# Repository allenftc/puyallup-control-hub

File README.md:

# Puyallup to Earth, Puyallup to Earth, can anyone hear me?
## No, because the loop times on REV control hubs are cooked. 30Hz should not be the standard for a control system. Even the EV3 is faster 💀💀💀
I am making the Puyallup Control Hub for fun just to see how overkill I can make a similar type of thing but for cheaper and more powerful, as well as smaller.

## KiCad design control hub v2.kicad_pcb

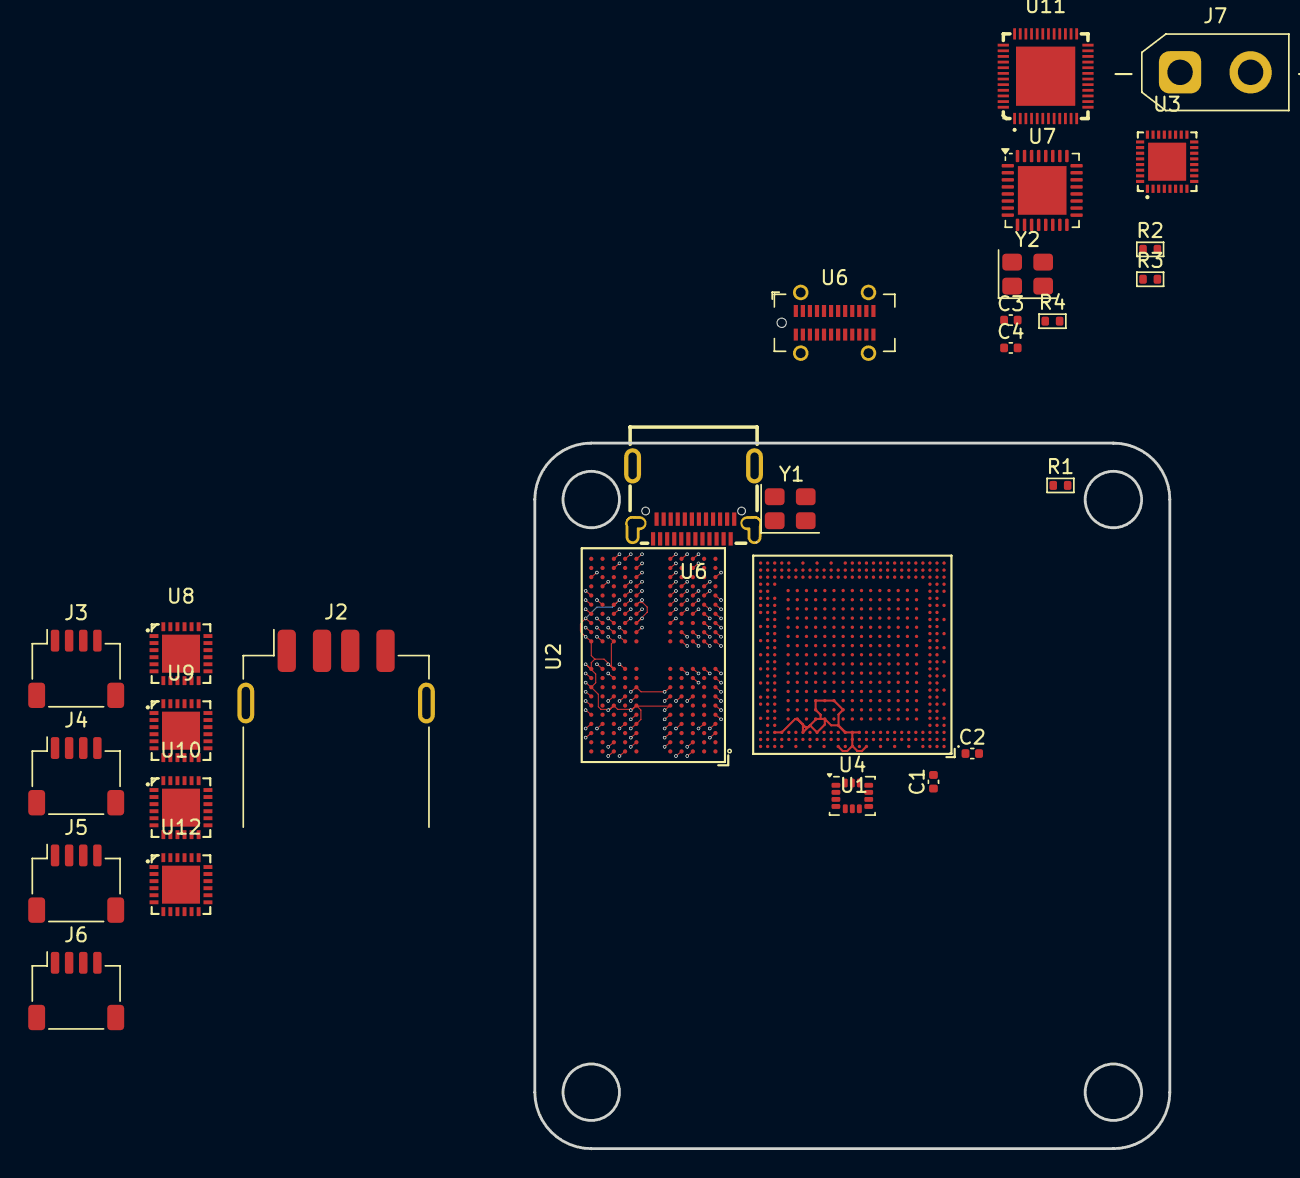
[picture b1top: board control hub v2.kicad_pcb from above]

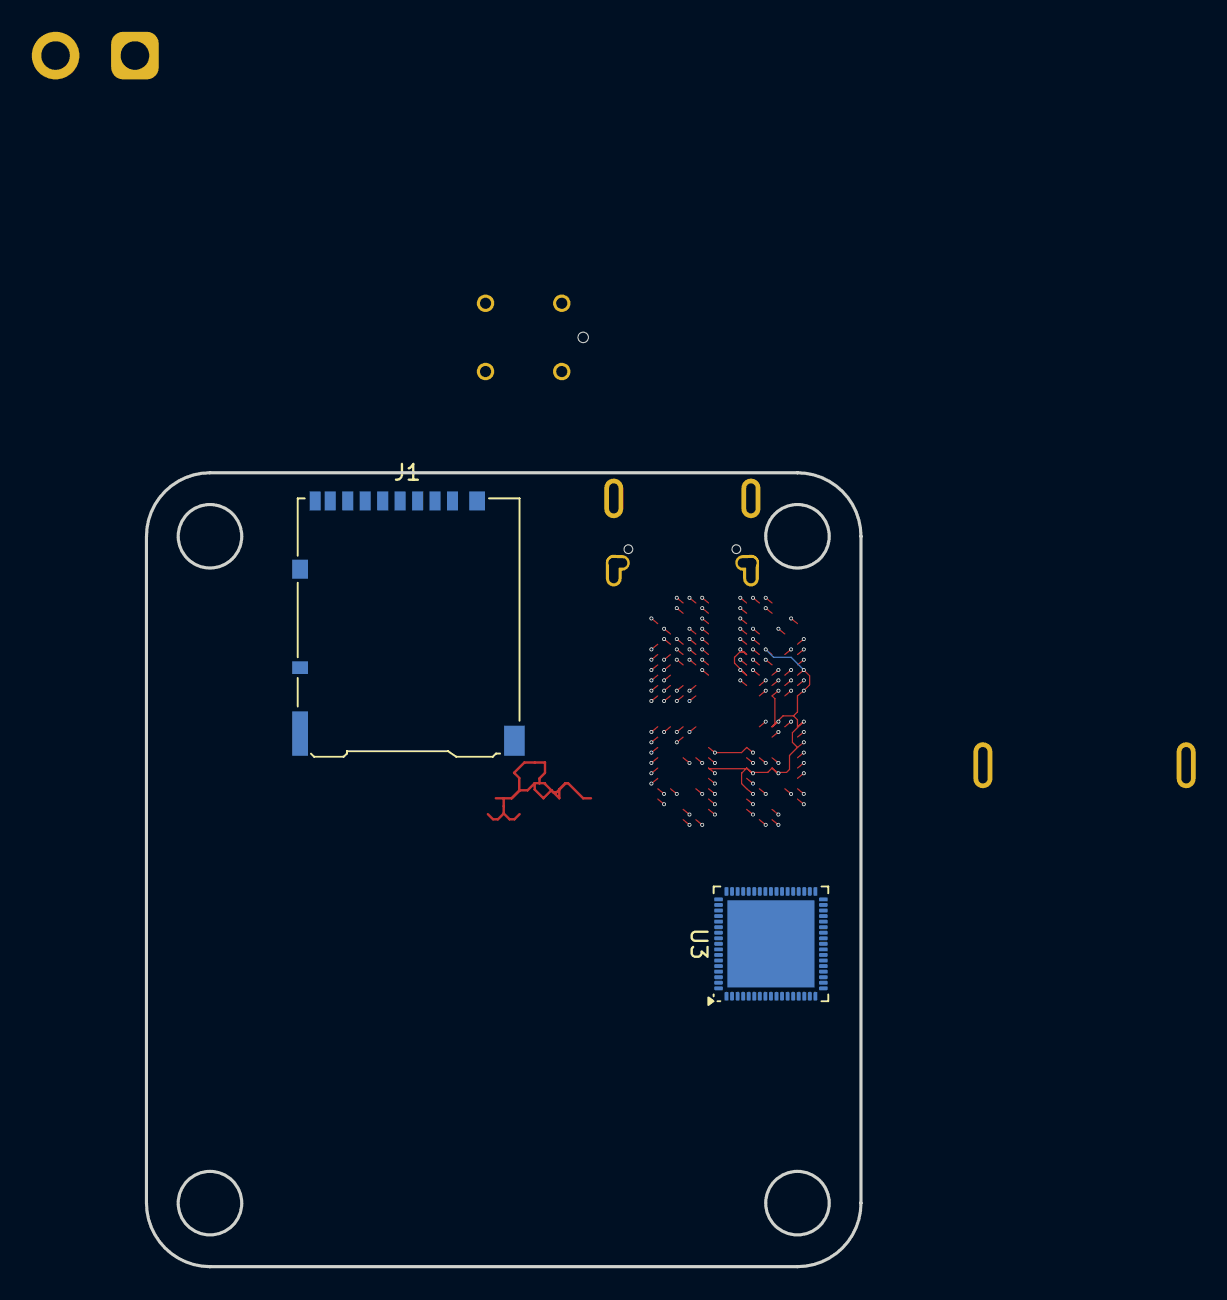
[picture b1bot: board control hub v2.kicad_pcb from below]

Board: 4 copper layers, 45.0 x 50.0 mm, 30 parts (2 on the bottom side), 98 nets.

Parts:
C1, C2, C3, C4: 18pF; C_0402_1005Metric
J1: Micro_SD_Card_Det2; microSD_HC_Hirose_DM3AT-SF-PEJM5
J2: USB_A; USB_A_Receptacle_GCT_USB1046
J3, J4, J5, J6: Conn_01x04_Socket; JST_SH_SM04B-SRSS-TB_1x04-1MP_P1.00mm_Horizontal
J7: Conn_01x02; AMASS_XT30UPB-M_1x02_P5.0mm_Vertical
R1, R4: 1M; R_0402_1005Metric
R2, R3: 240R; R_0402_1005Metric
U1: RK3562; BGA-478_L13.9-W13.9_RK3562
U2: H9HCNNNBKUMLXR-NEE; FBGA-200_L15.0-W10.0-BL_H9HCNNNBKUMLXR
U3: RT9992ZQW; WQFN-32_L4.0-W4.0-P0.40-BL-EP
U3#2: RK808-B; ArtInChip_QFN-68-1EP_7x7mm_P0.35mm_EP5.49x5.49mm
U4: LSM6DS3; LGA-14_3x2.5mm_P0.5mm_LayoutBorder3x4y
U6: GT-USB-7013A03; USB-C-SMD_GT-USB-7013A03
U6#2: GT-USB-7013A03; USB_C_Receptacle_GCT_USB4115-03-C
U7: STM32G431KBUx; QFN-32-1EP_5x5mm_P0.5mm_EP3.45x3.45mm
U8, U9, U10, U12: G2061Q; QFN-24_L4.0-W4.0-P0.50-TL-EP2.7
U11: RTL8723DS-CG; WQFN-48_L6.0-W6.0-P0.40-BL-EP4.2
Y1, Y2: 24; Crystal_SMD_3225-4Pin_3.2x2.5mm

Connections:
0V9: U1.1E12 (VDD_GPU_1), U1.1F11 (VDD_GPU_2), U1.1F12 (VDD_GPU_3), U1.1F13 (VDD_GPU_4), U1.1G3 (VDD_NPU_1), U1.1G4 (VDD_NPU_2), U1.1G5 (VDD_NPU_3), U1.1G8 (VDD_CPU_1), U1.1G10 (VDD_LOGIC_1), U1.1G11 (VDD_GPU_5), U1.1G12 (VDD_GPU_6), U1.1H3 (VDD_NPU_4), U1.1H4 (VDD_NPU_5), U1.1H6 (VDD_CPU_2), U1.1H7 (VDD_CPU_3), U1.1H8 (VDD_CPU_4), U1.1H10 (VDD_LOGIC_2), U1.1H11 (VDD_LOGIC_MEM), U1.1J6 (VDD_CPU_5), U1.1J7 (VDD_CPU_6), U1.1J10 (VDD_LOGIC_3), U1.1J11 (VDD_LOGIC_4), U1.1J12 (VDD_LOGIC_5), U1.1K10 (VDD_LOGIC_6), U1.1K14 (MULTI_PHY_AVDD_0V9), U1.1L6 (MIPI_CSI_RX1_AVDD_0V9), U1.1L8 (MIPI_CSI_RX0_AVDD_0V9), U1.1L14 (USB_AVDD_0V9), U1.1M9 (MIPI_DSI_TX/LVDS_TX_AVDD_0V9), U1.1M10 (SYSPLL_AVDD_0V9), U1.1M11 (PMU_VDD_LOGIC_0V9), U1.1M13 (PMUPLL_AVDD_0V9)
+1V1: U1.1D6 (DDRPHY_VDDQ_3), U1.1D11 (DDRPHY_VDDQ_6), U1.1E3 (DDRPHY_VDDQ_1), U1.1E4 (DDRPHY_VDDQL_1), U1.1E5 (DDRPHY_VDDQ_2), U1.1E6 (DDRPHY_VDDQL_2), U1.1E7 (DDRPHY_VDDQ_4), U1.1E8 (DDRPHY_VDDQL_3), U1.1E9 (DDRPHY_VDDQ_5)
+1V1_DDR: R2.1, R3.1, U2.A4 (VDD2), U2.A9 (VDD2), U2.AA3 (VDDQ), U2.AA5 (VDDQ), U2.AA8 (VDDQ), U2.AA10 (VDDQ), U2.AB4 (VDD2), U2.AB9 (VDD2), U2.B3 (VDDQ), U2.B5 (VDDQ), U2.B8 (VDDQ), U2.B10 (VDDQ), U2.D1 (VDDQ), U2.D5 (VDDQ), U2.D8 (VDDQ), U2.D12 (VDDQ), U2.F3 (VDDQ), U2.F5 (VDD2), U2.F8 (VDD2), U2.F10 (VDDQ), U2.H1 (VDD2), U2.H5 (VDD2), U2.H8 (VDD2), U2.H12 (VDD2), U2.K1 (VDD2), U2.K3 (VDD2), U2.K10 (VDD2), U2.K12 (VDD2), U2.N1 (VDD2), U2.N3 (VDD2), U2.N10 (VDD2), U2.N12 (VDD2), U2.R1 (VDD2), U2.R5 (VDD2), U2.R8 (VDD2), U2.R12 (VDD2), U2.U3 (VDDQ), U2.U5 (VDD2), U2.U8 (VDD2), U2.U10 (VDDQ), U2.W1 (VDDQ), U2.W5 (VDDQ), U2.W8 (VDDQ), U2.W12 (VDDQ)
+1V8: U1.1E14 (SARADC0_AVDD_1V8), U1.1E15 (OTP_VCC_1V8), U1.1G1 (SYSPLL_AVDD_1V8), U1.1H14 (VCCIO4), U1.1K2 (SARADC1_AVDD_1V8), U1.1K3 (VCCIO5), U1.1K15 (MULTI_PHY_AVDD_1V8), U1.1L5 (VCCIO6_2), U1.1L11 (PMUIO1), U1.1L13 (PMUPLL_AVDD_1V8), U1.1M4 (VCCIO6_1), U1.1M7 (MIPI_CSI_RX1_AVDD_1V8), U1.1M8 (MIPI_CSI_RX0_AVDD_1V8), U1.1M15 (USB_AVDD_1V8), U1.1N9 (MIPI_DSI_TX/LVDS_TX_AVDD_1V8)
+1V8_DDR: U2.F1 (VDD1), U2.F12 (VDD1), U2.G4 (VDD1), U2.G9 (VDD1), U2.T4 (VDD1), U2.T9 (VDD1), U2.U1 (VDD1), U2.U12 (VDD1)
+3.3V: J3.3, J4.3, J5.3, J6.3, U4.5 (VDDIO), U4.8 (VDD)
+3V3: J1.4 (VDD), U1.1F14 (VCCIO2), U1.1G15 (VCCIO3), U1.1L3 (VCCIO1), U1.1L12 (PMUIO0), U1.1M14 (USB_AVDD_3V3), U7.1 (VDD), U7.15 (VDDA), U7.17 (VDD)
+BATT: J7.1, U3.29 (BAT)
/Memory/DDR.A.a0: U1.B10 (AC11/DDR4_A11/LPDDR4_A0_A/DDR3_A6/LPDDR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), U2.H2 (CA0a)
/Memory/DDR.A.a1: U1.A10 (AC2/DDR4_A2/LPDDR4_A1_A/DDR3_A4/LPDDR3_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), U2.J2 (CA1a)
/Memory/DDR.A.a2: U1.C10 (AC15/DDR4_A15_CASN/LPDDR4_A2_A/DDR3_A0/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), U2.H9 (CA2a)
/Memory/DDR.A.a3: U1.1A6 (AC12/DDR4_A12/LPDDR4_A3_A/DDR3_BA0), U2.H10 (CA3a)
/Memory/DDR.A.a4: U1.1B8 (AC14/DDR4_A14_WEN/LPDDR4_A4_A/DDR3_A15), U2.H11 (CA4a)
/Memory/DDR.A.a5: U1.1A7 (AC16/DDR4_A16_RASN/LPDDR4_A5_A/DDR3_RASN), U2.J11 (CA5a)
/Memory/DDR.A.b0: U1.B18 (AC7/DDR4_A7/LPDDR4_A0_B/DDR3_A5/LPDDR3_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), U2.R2 (CA0b)
/Memory/DDR.A.b1: U1.A18 (AC6/DDR4_A6/LPDDR4_A1_B/DDR3_A14/LPDDR3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), U2.P2 (CA1b)
/Memory/DDR.A.b2: U1.C18 (AC18/DDR4_BA0/LPDDR4_A2_B/DDR3_A1/LPDDR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), U2.R9 (CA2b)
/Memory/DDR.A.b3: U1.1A10 (AC4/DDR4_A4/LPDDR4_A3_B/DDR3_BA1), U2.R10 (CA3b)
/Memory/DDR.A.b4: U1.1A9 (AC19/DDR4_BA1/LPDDR4_A4_B/DDR3_A12), U2.R11 (CA4b)
/Memory/DDR.A.b5: U1.1A8 (AC5/DDR4_A5/LPDDR4_A5_B/DDR3_A11), U2.P11 (CA5b)
/Memory/DDR.CKEa0: U1.C12 (AC22/DDR4_CKE0/LPDDR4_CKE0_A/DDR3_CKE/L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), U2.J4 (CKE0a)
/Memory/DDR.CKEb0: U1.C16 (AC10/DDR4_A10/LPDDR4_CKE0_B/DDR3_A10/LP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), U2.P4 (CKE0b)
/Memory/DDR.CLKa+: U1.B13 (AC24/DDR4_CLK0N/LPDDR4_CLKP_A/DDR3_CLKN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), U2.J8 (CK_ta)
/Memory/DDR.CLKa-: U1.A13 (AC23/DDR4_CLK0P/LPDDR4_CLKN_A/DDR3_CLKP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), U2.J9 (CK_ca)
/Memory/DDR.CLKb+: U1.B15 (AC9/DDR4_A9/LPDDR4_CLKP_B/DDR3_A13), U2.P8 (CK_tb)
/Memory/DDR.CLKb-: U1.A15 (AC0/DDR4_A0/LPDDR4_CLKN_B/DDR3_A9), U2.P9 (CK_cb)
/Memory/DDR.CS0A: U1.B11 (AC3/DDR4_A3/LPDDR4_CS0N_A/DDR3_ODT1/LPD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), U2.H4 (CS0a)
/Memory/DDR.CS0B: U1.B17 (AC28/DDR4_ODT1/LPDDR4_CS0N_B/DDR3_CS0N/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), U2.R4 (CS0b)
/Memory/DDR.DMA0: U1.B7 (DDR_DM0_A/DDR4_DML_A/LPDDR4_DM0_A/DDR3_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), U2.C3 (DMI0a)
/Memory/DDR.DMA1: U1.A2 (DDR_DM1_A/DDR4_DMU_A/LPDDR4_DM1_A/DDR3_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), U2.C10 (DMI1a)
/Memory/DDR.DMB1: U1.A26 (DDR_DM1_B/DDR4_DML_B/LPDDR4_DM1_B/DDR3_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), U2.Y10 (DMI1b)
/Memory/DDR.DQSa+0: U1.1A3 (DDR_DQS0P_A/DDR4_DQSL_P_A/LPDDR4_DQS0P_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), U2.D3 (DQS0_ta)
/Memory/DDR.DQSa+1: U1.1A1 (DDR_DQS1P_A/DDR4_DQSU_P_A/LPDDR4_DQS1P_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), U2.D10 (DQS1_ta)
/Memory/DDR.DQSa-0: U1.1B3 (DDR_DQS0N_A/DDR4_DQSL_N_A/LPDDR4_DQS0N_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), U2.E3 (DQS0_ca), U2.V3 (DQS0_cb)
/Memory/DDR.DQSa-1: U1.1B1 (DDR_DQS1N_A/DDR4_DQSU_N_A/LPDDR4_DQS1N_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), U2.E10 (DQS1_ca)
/Memory/DDR.DQSb+0: U1.1A13 (DDR_DQS0P_B/DDR4_DQSU_P_B/LPDDR4_DQS0P_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), U2.W3 (DQS0_tb)
/Memory/DDR.DQSb+1: U1.1A15 (DDR_DQS1P_B/DDR4_DQSL_P_B/LPDDR4_DQS1P_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), U2.W10 (DQS1_tb)
/Memory/DDR.DQSb-1: U1.1B15 (DDR_DQS1N_B/DDR4_DQSL_N_B/LPDDR4_DQS1N_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), U2.V10 (DQS1_cb)
/Memory/DDR.DQa0: U1.B6 (DDR_DQ0_A/DDR4_DQL6_A/LPDDR4_DQ0_A/DDR3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), U2.B2 (DQ0a)
/Memory/DDR.DQa1: U1.B8 (DDR_DQ1_A/DDR4_DQL2_A/LPDDR4_DQ1_A/DDR3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), U2.C2 (DQ1a)
/Memory/DDR.DQa2: U1.A8 (DDR_DQ2_A/DDR4_DQL0_A/LPDDR4_DQ2_A/DDR3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), U2.E2 (DQ2a)
/Memory/DDR.DQa3: U1.C8 (DDR_DQ3_A/DDR4_DQL4_A/LPDDR4_DQ3_A/DDR3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), U2.F2 (DQ3a)
/Memory/DDR.DQa4: U1.C5 (DDR_DQ4_A/DDR4_DQL5_A/LPDDR4_DQ4_A/DDR3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), U2.F4 (DQ4a)
/Memory/DDR.DQa5: U1.B5 (DDR_DQ5_A/DDR4_DQL1_A/LPDDR4_DQ5_A/DDR3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), U2.E4 (DQ5a)
/Memory/DDR.DQa6: U1.A6 (DDR_DQ6_A/DDR4_DQL7_A/LPDDR4_DQ6_A/DDR3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), U2.C4 (DQ6a)
/Memory/DDR.DQa7: U1.C6 (DDR_DQ7_A/DDR4_DQL3_A/LPDDR4_DQ7_A/DDR3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), U2.B4 (DQ7a)
/Memory/DDR.DQa8: U1.C2 (DDR_DQ8_A/DDR4_DQU1_A/LPDDR4_DQ8_A/DDR3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), U2.B11 (DQ8a)
/Memory/DDR.DQa9: U1.C1 (DDR_DQ9_A/DDR4_DQU5_A/LPDDR4_DQ9_A/DDR3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), U2.C11 (DQ9a)
/Memory/DDR.DQa10: U1.B1 (DDR_DQ10_A/DDR4_DQU3_A/LPDDR4_DQ10_A/DD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), U2.E11 (DQ10a)
/Memory/DDR.DQa11: U1.B2 (DDR_DQ11_A/DDR4_DQU7_A/LPDDR4_DQ11_A/DD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), U2.F11 (DQ11a)
/Memory/DDR.DQa12: U1.A4 (DDR_DQ12_A/DDR4_DQU0_A/LPDDR4_DQ12_A/DD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), U2.F9 (DQ12a)
/Memory/DDR.DQa13: U1.B4 (DDR_DQ13_A/DDR4_DQU4_A/LPDDR4_DQ13_A/DD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), U2.E9 (DQ13a)
/Memory/DDR.DQa14: U1.A3 (DDR_DQ14_A/DDR4_DQU2_A/LPDDR4_DQ14_A/DD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), U2.C9 (DQ14a)
/Memory/DDR.DQa15: U1.B3 (DDR_DQ15_A/DDR4_DQU6_A/LPDDR4_DQ15_A/DD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), U2.B9 (DQ15a)
/Memory/DDR.DQb0: U1.B22 (DDR_DQ0_B/DDR4_DQU7_B/LPDDR4_DQ0_B/DDR3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), U2.AA2 (DQ0b)
/Memory/DDR.DQb1: U1.B20 (DDR_DQ1_B/DDR4_DQU3_B/LPDDR4_DQ1_B/DDR3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), U2.Y2 (DQ1b)
/Memory/DDR.DQb2: U1.A20 (DDR_DQ2_B/DDR4_DQU1_B/LPDDR4_DQ2_B/DDR3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), U2.V2 (DQ2b)
/Memory/DDR.DQb3: U1.C20 (DDR_DQ3_B/DDR4_DQU5_B/LPDDR4_DQ3_B/DDR3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), U2.U2 (DQ3b)
/Memory/DDR.DQb4: U1.C23 (DDR_DQ4_B/DDR4_DQU0_B/LPDDR4_DQ4_B/DDR3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), U2.U4 (DQ4b)
/Memory/DDR.DQb5: U1.B23 (DDR_DQ5_B/DDR4_DQU4_B/LPDDR4_DQ5_B/DDR3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), U2.V4 (DQ5b)
/Memory/DDR.DQb6: U1.C22 (DDR_DQ6_B/DDR4_DQU2_B/LPDDR4_DQ6_B/DDR3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), U2.Y4 (DQ6b)
/Memory/DDR.DQb7: U1.A22 (DDR_DQ7_B/DDR4_DQU6_B/LPDDR4_DQ7_B/DDR3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), U2.AA4 (DQ7b)
/Memory/DDR.DQb8: U1.C26 (DDR_DQ8_B/DDR4_DQL0_B/LPDDR4_DQ8_B/DDR3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), U2.AA11 (DQ8b)
/Memory/DDR.DQb9: U1.C27 (DDR_DQ9_B/DDR4_DQL4_B/LPDDR4_DQ9_B/DDR3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), U2.Y11 (DQ9b)
/Memory/DDR.DQb10: U1.B27 (DDR_DQ10_B/DDR4_DQL2_B/LPDDR4_DQ10_B/DD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), U2.V11 (DQ10b)
/Memory/DDR.DQb11: U1.B26 (DDR_DQ11_B/DDR4_DQL6_B/LPDDR4_DQ11_B/DD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), U2.U11 (DQ11b)
/Memory/DDR.DQb12: U1.A24 (DDR_DQ12_B/DDR4_DQL5_B/LPDDR4_DQ12_B/DD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), U2.U9 (DQ12b)
/Memory/DDR.DQb13: U1.B24 (DDR_DQ13_B/DDR4_DQL7_B/LPDDR4_DQ13_B/DD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), U2.V9 (DQ13b)
/Memory/DDR.DQb14: U1.A25 (DDR_DQ14_B/DDR4_DQL1_B/LPDDR4_DQ14_B/DD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), U2.Y9 (DQ14b)
/Memory/DDR.DQb15: U1.B25 (DDR_DQ15_B/DDR4_DQL3_B/LPDDR4_DQ15_B/DD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), U2.AA9 (DQ15b)
/Memory/DDR.ODTa0: U1.B9 (AC8/DDR4_A8/LPDDR4_ODT0_CA_A/DDR3_A7/LP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), U2.G2 (ODTa)
/Memory/DDR.ODTb0: U1.B19 (AC13/DDR4_A13/LPDDR4_ODT0_CA_B/DDR3_A8/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), U2.T2 (ODTb)
/Memory/DDR.RST: U1.1B11 (AC29/DDR4_RESETN/LPDDR4_RESETN/DDR3_RES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), U2.T11 (RESET)
/Peripherals/SDMMC0.CLK: J1.5 (CLK), U1.P27 (SDMMC0_CLK/TEST_CLK_OUT/UART5_TX_M0/SPI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)
/Peripherals/SDMMC0.CMD: J1.3 (CMD), U1.P25 (SDMMC0_CMD/SPDIF_TX_M2/UART5_RX_M0/GPIO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)
/Peripherals/SDMMC0.D0: J1.7 (DAT0), U1.R25 (SDMMC0_D0/UART0_RX_M1/UART7_RX_M1/SPI1_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)
/Peripherals/SDMMC0.D1: J1.8 (DAT1), U1.R26 (SDMMC0_D1/UART0_TX_M1/UART7_TX_M1/SPI1_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)
/Peripherals/SDMMC0.D2: J1.1 (DAT2), U1.N25 (SDMMC0_D2/JTAG_CPU_MCU_TCK_M1/UART5_CTS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)
/Peripherals/SDMMC0.D3: J1.2 (DAT3/CD), U1.N26 (SDMMC0_D3/JTAG_CPU_MCU_TMS_M1/UART5_RTS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)
/Peripherals/SDMMC0.DET: J1.10 (DET_A), U1.1R15 (SDMMC0_DETN/I2C4_SDA_M1/GPIO0_A4_u)
/Peripherals/SDMMC1.CLK: U1.U25 (SDMMC1_CLK/RGMII_RXCLK_M1/I2S0_MCLK_M1/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), U11.31 (SD_CLK/GSPI_CLK)
/Peripherals/SDMMC1.CMD: U1.T27 (SDMMC1_CMD/RGMII_RXD3_M1/I2S0_SCLK_M1/P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), U11.32 (SD_CMD/GSPI_DI)
/Peripherals/SDMMC1.D0: U1.U26 (SDMMC1_D0/RGMII_TXD2_M1/I2S0_SDI0_M1/PW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), U11.30 (SD_D0/GSPI_DO)
/Peripherals/SDMMC1.D1: U1.V25 (SDMMC1_D1/RGMII_TXD3_M1/I2S0_SDI1_M1/PW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), U11.29 (SD_D1/GSPI_INT)
/Peripherals/SDMMC1.D2: U1.T25 (SDMMC1_D2/RGMII_TXCLK_M1/I2S0_SDO0_M1/P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), U11.34 (SD_D2)
/Peripherals/SDMMC1.D3: U1.T26 (SDMMC1_D3/RGMII_RXD2_M1/I2S0_LRCK_M1/PW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), U11.33 (SD_D3/GSPI_CS#)
/Peripherals/UART0.RX: U1.Y25 (UART1_RX_M0/RGMII_TXD0_M1/I2S0_SDO1_M1/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), U11.27 (UART_OUT)
/Peripherals/UART0.TX: U1.Y26 (UART1_TX_M0/RGMII_TXD1_M1/I2S0_SDO2_M1/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), U11.25 (UART_IN)
/Peripherals/USB2_D+: J2.3 (D+), U1.AE27 (USB20_HOST1_DP)
/Peripherals/USB2_D-: J2.2 (D-), U1.AE26 (USB20_HOST1_DM)
GND: C1.2, C2.2, C3.2, C4.2, J1.6 (VSS), J1.11 (SHIELD), J2.4 (GND), J2.5 (Shield), J3.4, J4.4, J5.4, J6.4, U1.1A2 (VSS_1A2), U1.1A4 (VSS_1A4), U1.1A5 (VSS_1A5), U1.1A11 (VSS_1A11), U1.1A12 (VSS_1A12), U1.1A14 (VSS_1A14), U1.1B2 (VSS_1B2), U1.1B4 (VSS_1B4), U1.1B5 (VSS_1B5), U1.1B9 (VSS_1B9), U1.1B12 (VSS_1B12), U1.1B14 (VSS_1B14), U1.1C1 (VSS_1C1), U1.1C2 (VSS_1C2), U1.1C3 (VSS_1C3), U1.1C4 (VSS_1C4), U1.1C5 (VSS_1C5), U1.1C6 (VSS_1C6), U1.1C7 (VSS_1C7), U1.1C10 (VSS_1C10), U1.1C11 (VSS_1C11), U1.1C12 (VSS_1C12), U1.1C13 (VSS_1C13), U1.1C14 (VSS_1C14), U1.1C15 (VSS_1C15), U1.1D1 (VSS_1D1), U1.1D2 (VSS_1D2), U1.1D3 (VSS_1D3), U1.1D7 (VSS_1D7), U1.1D8 (VSS_1D8), U1.1D9 (VSS_1D9), U1.1D10 (VSS_1D10), U1.1D12 (VSS_1D12), U1.1D13 (VSS_1D13), U1.1D14 (VSS_1D14), U1.1D15 (VSS_1D15), U1.1E2 (VSS_1E2), U1.1E11 (VSS_1E11), U1.1E13 (VSS_1E13), U1.1F3 (VSS_1F3), U1.1F4 (VSS_1F4), U1.1F5 (VSS_1F5), U1.1F7 (VSS_1F7), U1.1F9 (VSS_1F9), U1.1F10 (VSS_1F10), U1.1F15 (VSS_1F15), U1.1G2 (VSS_1G2), U1.1G6 (VSS_1G6), U1.1G7 (VSS_1G7), U1.1G9 (VSS_1G9), U1.1G13 (VSS_1G13), U1.1G14 (VSS_1G14), U1.1H2 (VSS_1H2), U1.1H5 (VSS_1H5), U1.1H9 (VSS_1H9), U1.1H12 (VSS_1H12), U1.1H13 (VSS_1H13), U1.1J3 (VSS_1J3), U1.1J4 (VSS_1J4), U1.1J5 (VSS_1J5), U1.1J8 (VSS_1J8), U1.1J9 (VSS_1J9), U1.1J13 (VSS_1J13), U1.1K4 (VSS_1K4), U1.1K5 (VSS_1K5), U1.1K6 (VSS_1K6), U1.1K7 (VSS_1K7), U1.1K8 (VSS_1K8), U1.1K9 (VSS_1K9), U1.1K11 (VSS_1K11), U1.1K12 (VSS_1K12), U1.1K13 (VSS_1K13), U1.1L4 (VSS_1L4), U1.1L7 (AVSS1_1L7), U1.1L9 (AVSS1_1L9), U1.1L10 (VSS_1L10), U1.1L15 (AVSS2_1L15), U1.1M3 (VSS_1M3), U1.1M5 (VSS_1M5), U1.1M6 (AVSS1_1M6), U1.1M12 (PMUPLL_AVSS), U1.1N1 (VSS_1N1), U1.1N2 (VSS_1N2), U1.1N3 (VSS_1N3), U1.1N4 (VSS_1N4), U1.1N5 (AVSS1_1N5), U1.1N6 (AVSS1_1N6), U1.1N7 (AVSS1_1N7), U1.1N8 (AVSS1_1N8), U1.1N10 (AVSS1_1N10), U1.1N11 (VSS_1N11), U1.1N12 (VSS_1N12), U1.1N13 (TVSS), U1.1N14 (AVSS2_1N14), U1.1N15 (AVSS2_1N15), U1.1P1 (AVSS1_1P1), U1.1P2 (AVSS1_1P2), U1.1P4 (AVSS1_1P4), U1.1P5 (AVSS1_1P5), U1.1P6 (AVSS1_1P6), U1.1P8 (AVSS1_1P8), U1.1P9 (AVSS1_1P9), U1.1P10 (AVSS1_1P10), U1.1P11 (VSS_1P11), U1.1P13 (VSS_1P13), U1.1R1 (AVSS1_1R1), U1.1R2 (AVSS1_1R2), U1.1R4 (AVSS1_1R4), U1.1R5 (AVSS1_1R5), U1.1R6 (AVSS1_1R6), U1.1R8 (AVSS1_1R8), U1.1R9 (AVSS1_1R9), U1.1R10 (AVSS1_1R10), U1.1R12 (VSS_1R12), U1.1R14 (VSS_1R14), U1.A1 (VSS_A1), U1.A12 (VSS_A12), U1.A16 (VSS_A16), U1.A27 (VSS_A27), U1.AA26 (AVSS2_AA26), U1.AA27 (VSS_AA27), U1.AB25 (AVSS2_AB25), U1.AC3 (AVSS1_AC3), U1.AD3 (AVSS1_AD3), U1.AD25 (AVSS2_AD25), U1.AE2 (AVSS1_AE2), U1.AE3 (AVSS1_AE3), U1.AE4 (AVSS1_AE4), U1.AE5 (AVSS1_AE5), U1.AE6 (AVSS1_AE6), U1.AE7 (AVSS1_AE7), U1.AE8 (AVSS1_AE8), U1.AE9 (AVSS1_AE9), U1.AE10 (AVSS1_AE10), U1.AE11 (AVSS1_AE11), U1.AE12 (AVSS1_AE12), U1.AE13 (AVSS1_AE13), U1.AE14 (AVSS1_AE14), U1.AE21 (VSS_AE21), U1.AE25 (VSS_AE25), U1.AF24 (VSS_AF24), U1.AG1 (AVSS1_AG1), U1.AG15 (VSS_AG15), U1.AG26 (VSS_AG26), U1.AG27 (AVSS2_AG27), U1.B14 (VSS_B14), U1.C3 (VSS_C3), U1.C4 (VSS_C4), U1.C7 (VSS_C7), U1.C9 (VSS_C9), U1.C13 (VSS_C13), U1.C14 (VSS_C14), U1.C15 (VSS_C15), U1.C19 (VSS_C19), U1.C21 (VSS_C21), U1.C24 (VSS_C24), U1.C25 (VSS_C25), U1.D2 (VSS_D2), U1.E3 (VSS_E3), U1.F3 (VSS_F3), U1.G25 (VSS_G25), U1.G27 (VSS_G27), U1.J3 (VSS_J3), U1.L25 (VSS_L25), U1.M27 (VSS_M27), U1.P26 (VSS_P26), U1.U3 (VSS_U3), U2.A3 (VSS), U2.A10 (VSS), U2.AB3 (VSS), U2.AB5 (VSS), U2.AB8 (VSS), U2.AB10 (VSS), U2.C1 (VSS), U2.C5 (VSS), U2.C8 (VSS), U2.C12 (VSS), U2.D2 (VSS), U2.D4 (VSS), U2.D9 (VSS), U2.D11 (VSS), U2.E1 (VSS), U2.E5 (VSS), U2.E8 (VSS), U2.E12 (VSS), U2.G1 (VSS), U2.G3 (VSS), U2.G5 (VSS), U2.G8 (VSS), U2.G10 (VSS), U2.G12 (VSS), U2.J1 (VSS), U2.J3 (VSS), U2.J10 (VSS), U2.J12 (VSS), U2.K2 (VSS), U2.K4 (VSS), U2.K9 (VSS), U2.K11 (VSS), U2.N2 (VSS), U2.N4 (VSS), U2.N9 (VSS), U2.N11 (VSS), U2.P1 (VSS), U2.P3 (VSS), U2.P10 (VSS), U2.P12 (VSS), U2.T1 (VSS), U2.T3 (VSS), U2.T5 (VSS), U2.T8 (VSS), U2.T10 (VSS), U2.T12 (VSS), U2.V1 (VSS), U2.V5 (VSS), U2.V8 (VSS), U2.V12 (VSS), U2.W2 (VSS), U2.W4 (VSS), U2.W9 (VSS), U2.W11 (VSS), U2.Y1 (VSS), U2.Y5 (VSS), U2.Y8 (VSS), U2.Y12 (VSS), U3#2.27 (GND2), U3#2.28 (GND2), U3#2.30 (AGND), U3#2.40 (GND1), U3#2.41 (GND1), U4.6 (GND), U4.7 (GND), U7.14 (VSSA), U7.16 (VSS), U7.32 (VSS), U7.33 (VSS), Y1.2, Y1.4, Y2.2, Y2.4
GNDPWR: J7.2, U3.33 (EP)
unnamed: C2.1, R1.1, U1.AG25 (OSC_SOC_XIN), Y1.1
unnamed: C1.1, R1.2, U1.AF25 (OSC_SOC_XOUT), Y1.3
unnamed: R3.2, U1.1D4 (DDR_RZQ)
unnamed: R2.2, U2.A5 (ZQ0)
unnamed: C3.1, R4.1, U11.15 (XI), Y2.1
unnamed: C4.1, R4.2, U11.16 (XO), Y2.3

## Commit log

2025-06-28 upload pcbs
2025-07-02 i understand
